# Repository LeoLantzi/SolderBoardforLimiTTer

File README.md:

# SolderBoardforLimiTTer
Ideas to solder LimiTTer componets on a pcb board instead of wiring, to make it simpler and save space.

worked for me, but put the charger bit outside not like intended.
The +3.3V pin  for the Sparkfun  usb lipo charger needs extra care in insulating to the arduino BLK pin, or scrap it off of and use an wire.
If I ever make an revision: As the first BM019pin is not used, cut it off. And make a small cutout on the board  and place usb port of the lipo charge .

made +20 if anybody wants them, message me

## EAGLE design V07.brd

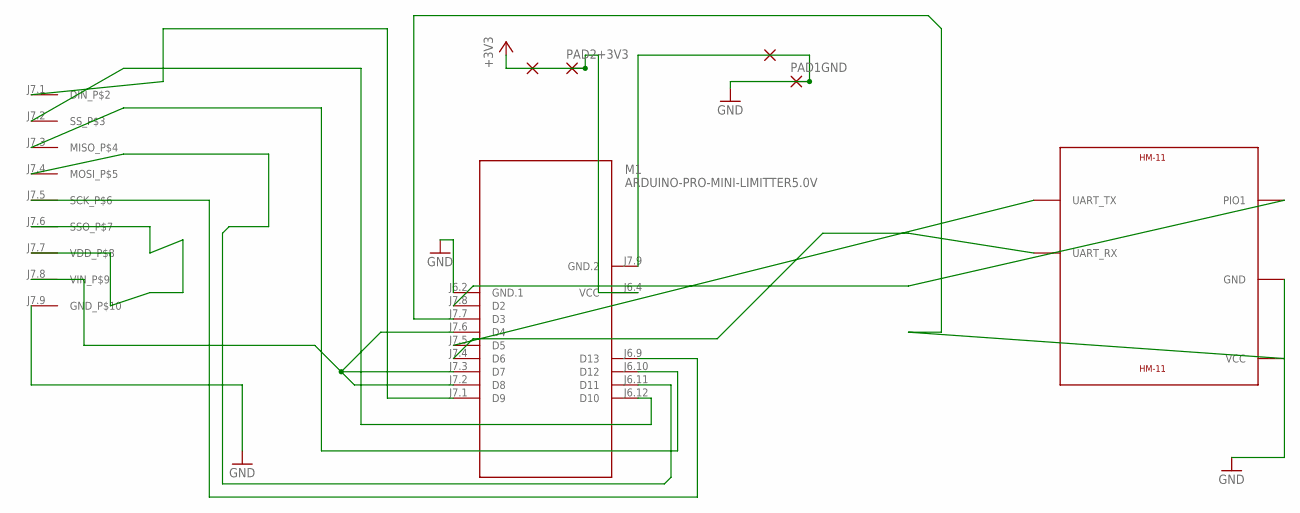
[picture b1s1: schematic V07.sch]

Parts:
M1: ARDUINO-PRO-MINI-LIMITTER5.0V; ARDUINO-PRO-MINI
PAD1GND, PAD2+3V3: 1,6/0,8
U$1: ARDUINO-9PIN1MM
U$2: HM-11

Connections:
+3V3: M1.J6.4 (VCC), PAD2+3V3.1
BLEVCC-D3: M1.J7.7 (D3), U$2.VCC
D2: M1.J7.8 (D2), U$2.PIO1
D5: M1.J7.5 (D5), U$2.UART_TX
D6: M1.J7.4 (D6), U$2.UART_RX
D10: M1.J6.12 (D10), U$1.J7.2 (SS_P$3)
D11: M1.J6.11 (D11), U$1.J7.4 (MOSI_P$5)
D12: M1.J6.10 (D12), U$1.J7.3 (MISO_P$4)
D13: M1.J6.9 (D13), U$1.J7.5 (SCK_P$6)
DINP2: M1.J7.1 (D9), U$1.J7.1 (DIN_P$2)
GND: M1.J6.2 (GND.1), M1.J7.9 (GND.2), PAD1GND.1, U$1.J7.9 (GND_P$10), U$2.GND
unnamed: U$1.J7.6 (SSO_P$7), U$1.J7.7 (VDD_P$8)
VINP9-D8D7D4: M1.J7.2 (D8), M1.J7.3 (D7), M1.J7.6 (D4), U$1.J7.8 (VIN_P$9)

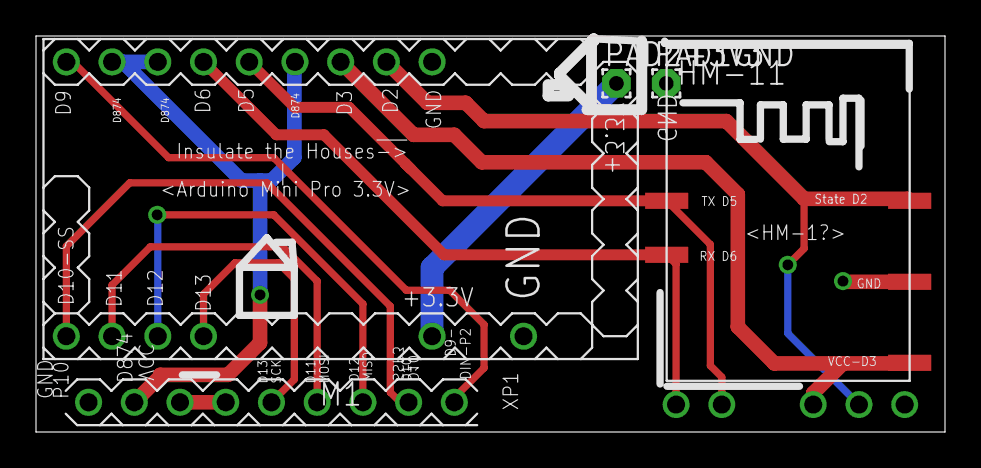
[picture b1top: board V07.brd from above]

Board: 2 copper layers, 50.5 x 22.0 mm, 5 parts (0 on the bottom side), 13 nets.

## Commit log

2017-05-21 long version and possible to cut to stack for higher
    currently waiting on the 0.8mm boards.
2017-05-21 Front mount Arduinio + hm1x
2017-05-21 Back mount BM019 and Sparkfun Charger
